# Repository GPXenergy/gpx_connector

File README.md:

# GPX Connector

The GPX-Connector is part of the GPX system to connect a smart meter to the GPX 
multi-user system. It runs on an ESP32, which connects to the smart meter 
through a RJ11 cable and sends the data over wifi to the GPX API. 

## Latest firmware

Check out the firmware directory for the latest firmware, separated by hardware 
version. You will find the firmware for your specific hardware in its own directory:

* gpx_connector_v1 (current prototype)
  * Latest firmware: gpx_connector_1.0.9.bin
* ...

## Local development setup

The project runs on [PlatformIO](https://platformio.org/), an open source 
framework and IDE for embedded development. 

This project has 2 platformio environments:
* __GPXConnector__ (default) - The final device / prototypes to run the system
* __wrover__ - The ESP-WROVER-kit device, used for debugging

Some platformio commands:
* `pio run`
  * Compile the program on default environment (GPXConnector)
* `pio run -t upload -e GPXConnector`
  * Compile and upload the program for specific environment
* `pio test -e wrover`
  * Run all the unit tests on the wrover environment

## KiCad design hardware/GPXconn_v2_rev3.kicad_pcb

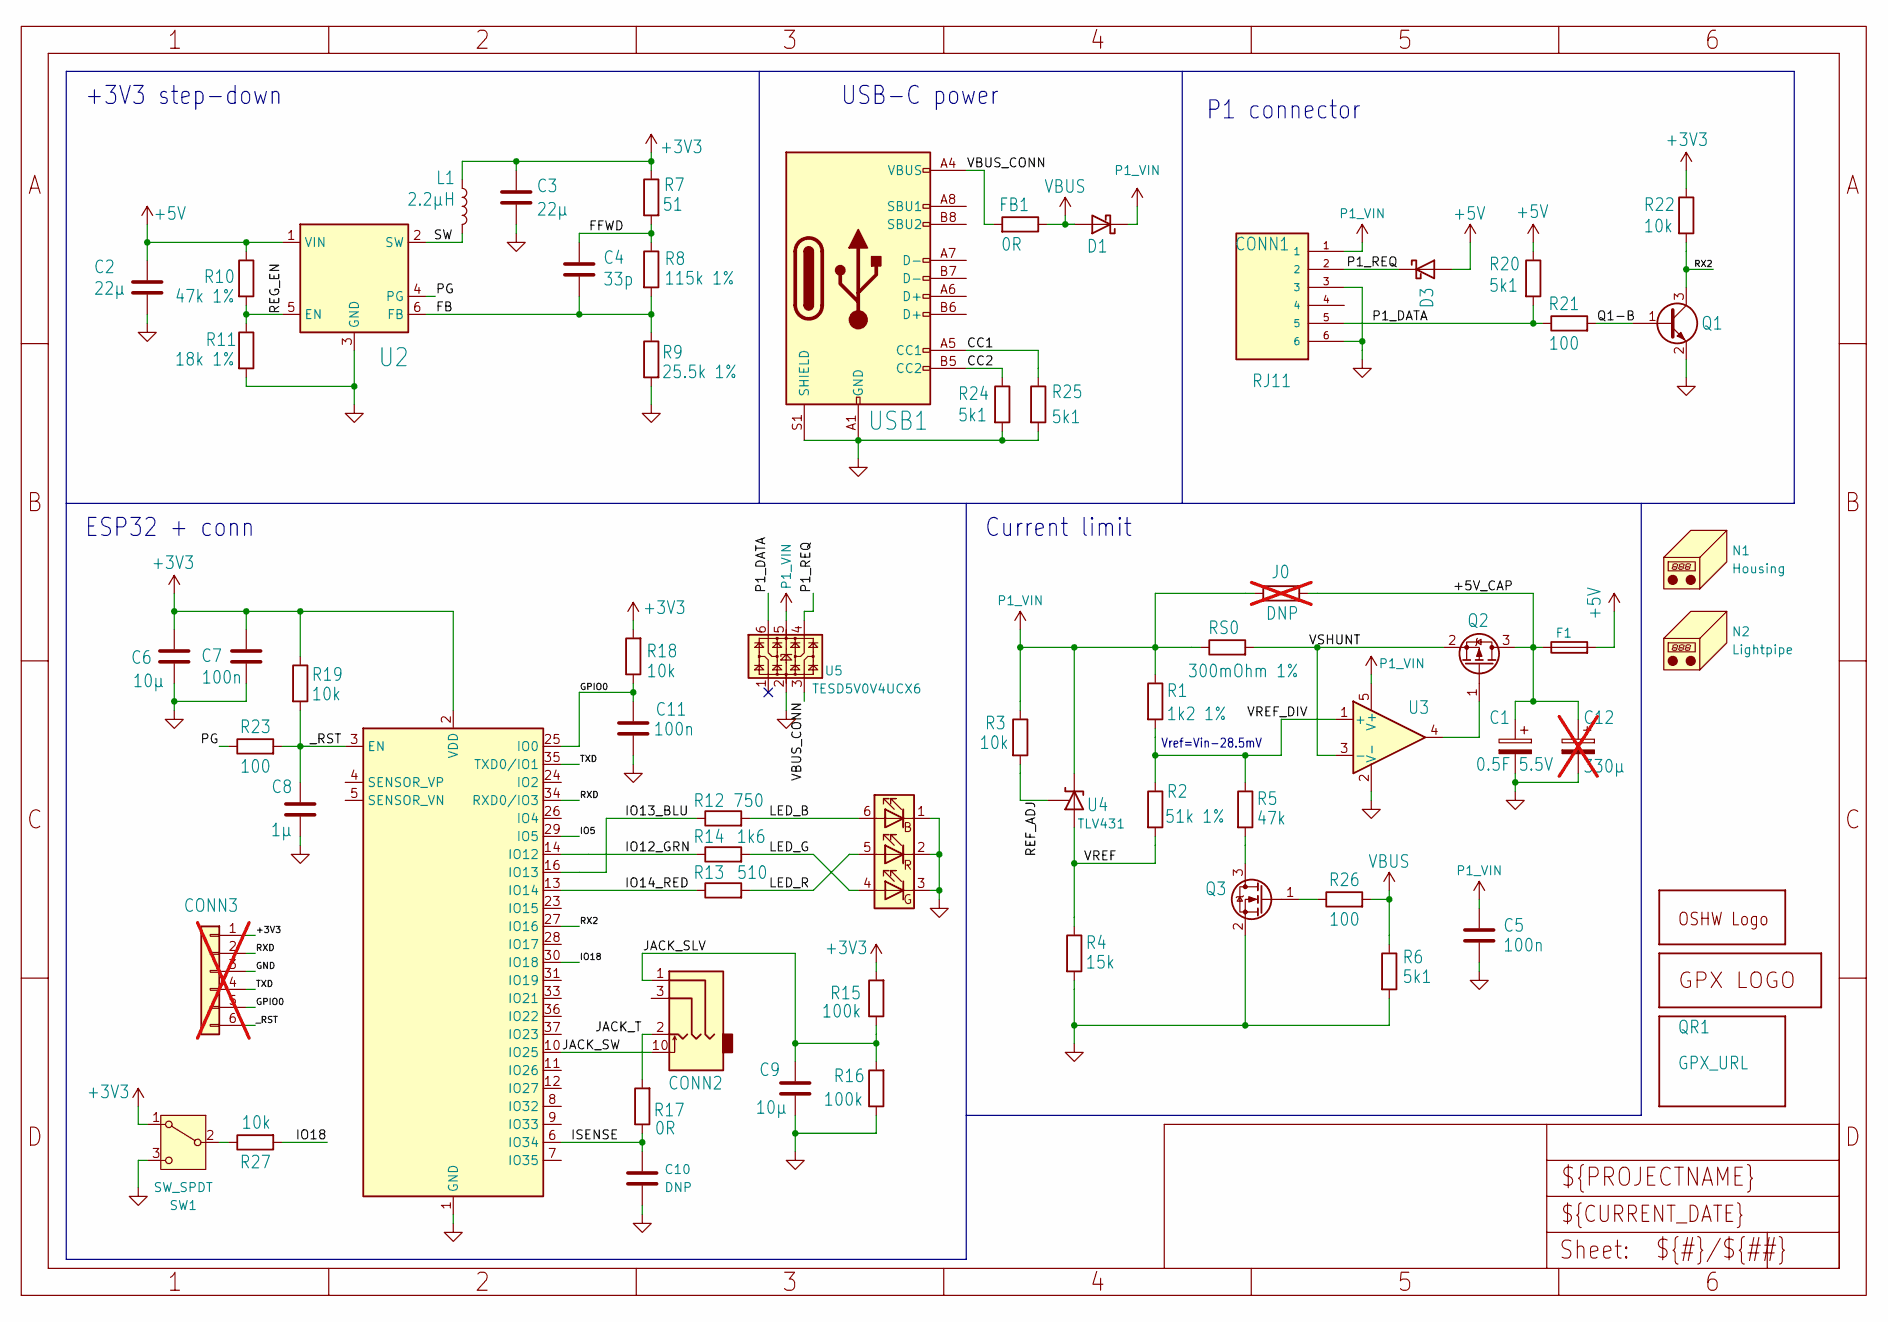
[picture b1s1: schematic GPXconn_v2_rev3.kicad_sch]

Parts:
C1: 0.5F 5.5V; CP_Radial_L17_W8.5_P12
C2, C3: 22µ; C_0805_2012Metric
C4: 33p; C_0603_1608Metric
C5, C7, C11: 100n; C_0603_1608Metric
C6, C9: 10µ; C_0603_1608Metric
C8: 1µ; C_0603_1608Metric
C10: DNP; C_0603_1608Metric
C12: 330µ; CP_Elec_6.3x7.7; not fitted
CONN1: RJ11; AMPHENOL_54601-906WPLF; PARTREV G
CONN2: JACK-3.5MM-3P-SW; CUI_SJ2-35813B-SMT-TR
CONN3: PINHD_R_1X62.54MM; PinHeader_1x06_P2.54mm_Vertical; not fitted
D1, D3: D-SCHOTTKY-SOD323-OL; D_SOD-323
F1: Fuse; Fuse_0603_1608Metric
FB1: 0R; R_0603_1608Metric
GOLD_ORB_SM1: OSHWLOGOLOGO8MM; OSHW-Symbol_6.7x6mm_SilkScreen
J0: DNP; R_0603_1608Metric; not fitted
L1: 2.2µH; L_1008_2520Metric
LED1: LED-RGB-NOCMN; LED_5050_3535_combined
N1: Housing; housing_TW5-3-7B
N2: Lightpipe; lightpipe_panelmount
Q1: MMBT3904; SOT23
Q2: DMP3099L-7; SOT23
Q3: 2N7002H; SOT23
QR1: GPX_URL; gpx_dash_qr_13x13
R1: 1k2 1%; R_0603_1608Metric
R2: 51k 1%; R_0603_1608Metric
R3, R18, R19, R22, R27: 10k; R_0603_1608Metric
R4: 15k; R_0603_1608Metric
R5: 47k; R_0603_1608Metric
R6, R20, R24, R25: 5k1; R_0603_1608Metric
R7: 51; R_0603_1608Metric
R8: 115k 1%; R_0603_1608Metric
R9: 25.5k 1%; R_0603_1608Metric
R10: 47k 1%; R_0603_1608Metric
R11: 18k 1%; R_0603_1608Metric
R12: 750; R_0603_1608Metric
R13: 510; R_0603_1608Metric
R14: 1k6; R_0603_1608Metric
R15, R16: 100k; R_0603_1608Metric
R17: 0R; R_0603_1608Metric
R21, R23, R26: 100; R_0603_1608Metric
RS0: 300mOhm 1%; R_0603_1608Metric
SW1: SW_SPDT; SW-1MS1-T2-B4-M6
U1: ESP-WROOM-3232D; ESP32-WROOM-32D
U2: TPS563252; SOT-563
U3: OPAMP_5PIN-NCS333A; SOT-353_SC-70-5
U4: TLV431; SOT23
U5: TESD5V0V4UCX6; SOT457
U$1: GPX_LOGO; gpx_logo
USB1: USB-C-2.0-16P; USB_C_Receptacle_GCT_USB4105-xx-A_16P_TopMnt_Horizontal

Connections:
+3V3: C3.2, C6.2, C7.2, CONN3.1, L1.2, R7.1, R15.2, R18.2, R19.1, R22.1, SW1.1 (A), U1.2 (VDD)
+5V: C2.2, D3.2 (A), F1.2, R10.1, R20.1, U2.1 (VIN)
/+5V_CAP: C1.1, C12.1, F1.1, J0.2, Q2.3 (D)
/CC1: R25.1, USB1.A5 (CC1)
/CC2: R24.1, USB1.B5 (CC2)
/FB: C4.2, R8.2, R9.1, U2.6 (FB)
/FFWD: C4.1, R7.2, R8.1
/GPIO0: C11.1, CONN3.5, R18.1, U1.25 (IO0)
/IO5: U1.29 (IO5)
/IO12_GRN: R14.1, U1.14 (IO12)
/IO13_BLU: R12.1, U1.16 (IO13)
/IO14_RED: R13.1, U1.13 (IO14)
/IO18: R27.2, U1.30 (IO18)
/ISENSE: C10.1, R17.1, U1.6 (IO34)
/JACK_SLV: C9.2, CONN2.1, R15.1, R16.2
/JACK_SW: CONN2.10, U1.10 (IO25)
/JACK_T: CONN2.2, R17.2
/LED_B: LED1.6 (BA), R12.2
/LED_G: LED1.4 (RA), R14.2
/LED_R: LED1.5 (GA), R13.2
/P1_DATA: CONN1.5, R20.2, R21.1, U5.6
/P1_REQ: CONN1.2, D3.1 (K), U5.4
/PG: R23.1, U2.4 (PG)
/Q1-B: Q1.1 (B), R21.2
/REF_ADJ: R3.2, U4.1 (REF)
/REG_EN: R10.2, R11.1, U2.5 (EN)
/RX2: Q1.3 (C), R22.2, U1.27 (IO16)
/RXD: CONN3.2, U1.34 (RXD0/IO3)
/SW: L1.1, U2.2 (SW)
/TXD: CONN3.4, U1.35 (TXD0/IO1)
/VBUS_CONN: FB1.2, U5.3, USB1.A4 (VBUS), USB1.A9 (VBUS), USB1.B4 (VBUS), USB1.B9 (VBUS)
/VREF: R2.2, R4.1, U4.3 (A)
/VREF_DIV: R1.2, R2.1, R5.1, U3.1 (+)
/VSHUNT: Q2.2 (S), RS0.2, U3.3 (-)
/_RST: C8.1, CONN3.6, R19.2, R23.2, U1.3 (EN)
GND: C1.2, C2.1, C3.1, C5.2, C6.1, C7.1, C8.2, C9.1, C10.2, C11.2, C12.2, CONN1.3, CONN1.6, CONN3.3, LED1.1 (BK), LED1.2 (GK), LED1.3 (RK), Q1.2 (E), Q3.2 (S), R4.2, R6.2, R9.2, R11.2, R16.1, R24.2, R25.2, SW1.3 (C), U1.1 (GND), U1.15 (GND), U1.38 (GND), U1.39 (GND), U2.3 (GND), U3.2 (V-), U5.2, USB1.A1 (GND), USB1.A12 (GND), USB1.B1 (GND), USB1.B12 (GND), USB1.S1 (SHIELD)
unnamed: Q2.1 (G), U3.4
unnamed: Q3.3 (D), R5.2
unnamed: Q3.1 (G), R26.1
unnamed: R27.1, SW1.2 (B)
P1_VIN: C5.1, CONN1.1, D1.1 (K), J0.1, R1.1, R3.1, RS0.1, U3.5 (V+), U4.2 (K), U5.5
VBUS: D1.2 (A), FB1.1, R6.1, R26.2

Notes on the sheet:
ESP32 + conn
USB-C power
Current limit
P1 connector
Vref=Vin-28.5mV
+3V3 step-down

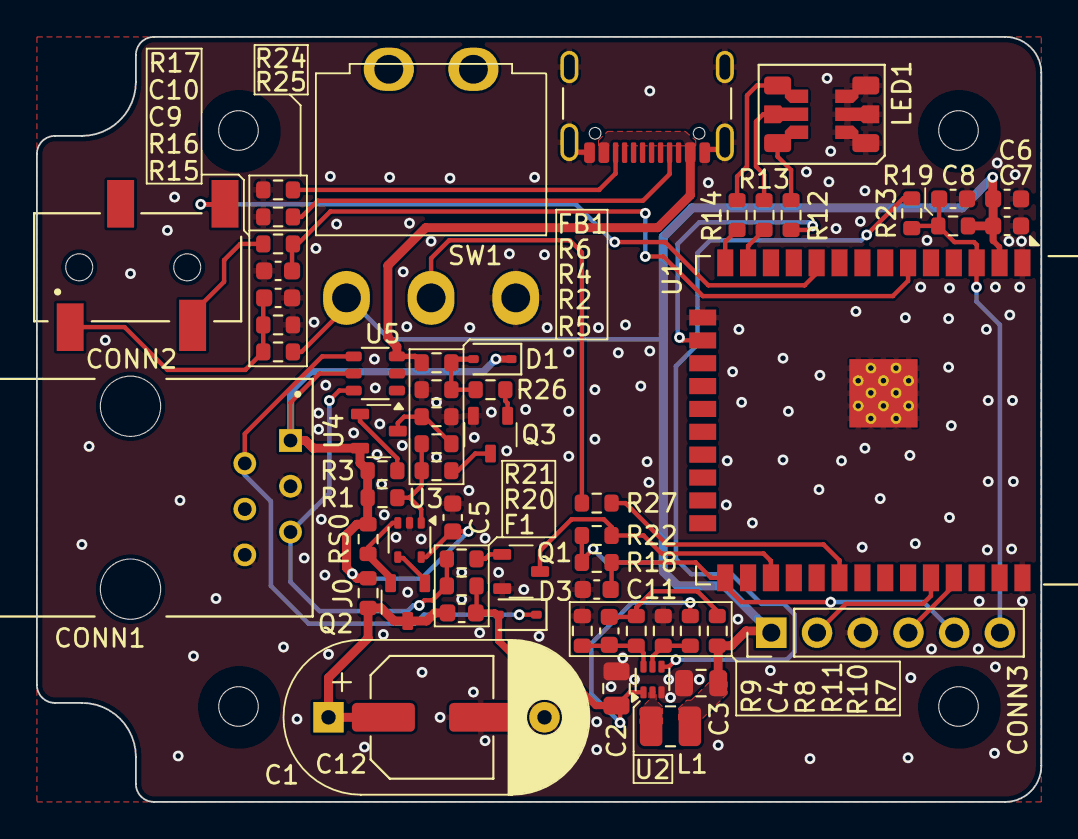
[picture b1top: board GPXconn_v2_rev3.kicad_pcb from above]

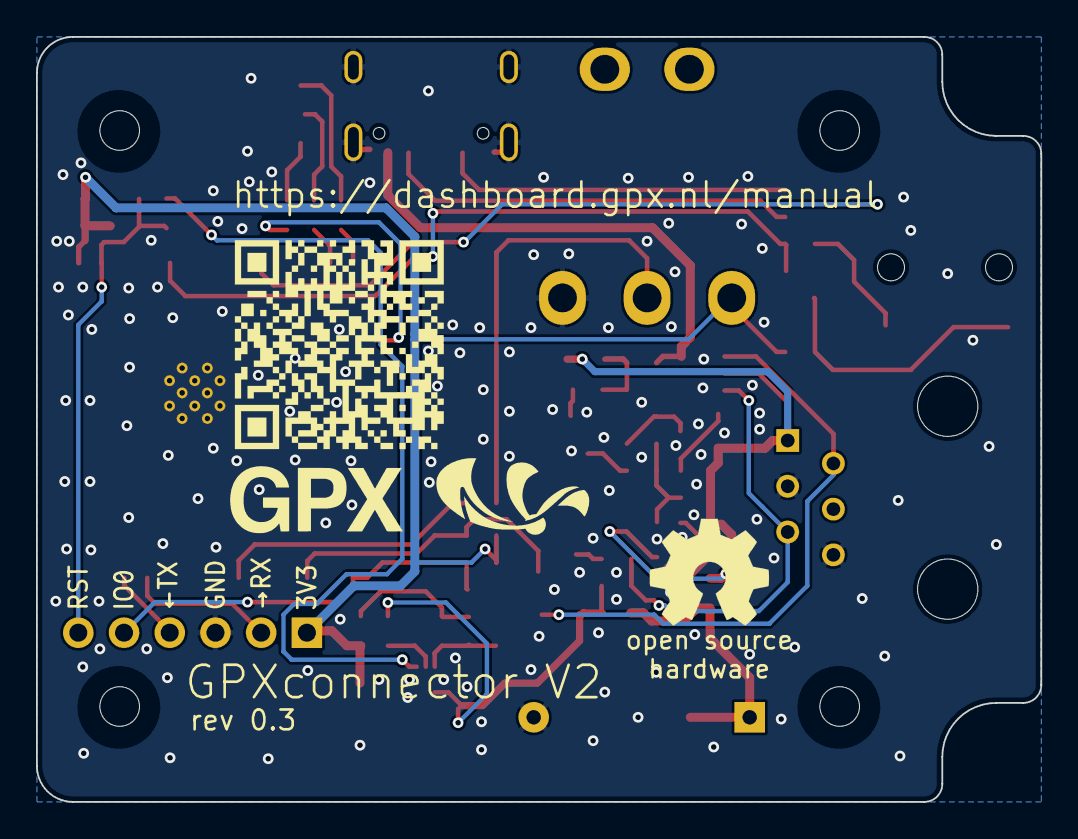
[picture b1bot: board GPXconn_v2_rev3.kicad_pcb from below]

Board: 2 copper layers, 55.8 x 42.5 mm, 65 parts (3 on the bottom side), 41 nets.

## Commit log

2021-01-18 initial commit transfer to github
2021-01-18 add firmware.bin
2021-04-07 add firmware copy script after release build, version number in platformio.ini, updated code with fixes
2021-04-07 update status led colors, changed text for OTA update complete
2021-04-14 add dsmr 2.2 support and test, fix config page to update meter connection baudrate and parity
2021-04-17 fix parity config for serial connection, update version
2021-04-20 fix inverter connector watts calculation for different current sensors
2021-04-30 add reset config button
2021-05-01 add threshold for 30A/1V current sensors, add dev build filenames
2021-05-05 cleanup non-debug serial logs
2021-05-26 add separate option for 1 or 3 phase power, update config pages and local storage
2021-05-28 add license
2021-05-29 update license
2021-10-11 Update README.md
    Latest firmware was gpx_connector_v1, now: gpx_connector_v1.0.7
2023-07-22 fix user api connector agent, added support for gas meter on separate bus
2023-09-23 v1.0.9 - fixes LED for success connection
2026-03-30 add hardware design files
